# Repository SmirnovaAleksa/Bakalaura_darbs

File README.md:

# Bakalaura_darbs
Working with ESP32 and STM32 for plant monitoring system

Final board

3D view

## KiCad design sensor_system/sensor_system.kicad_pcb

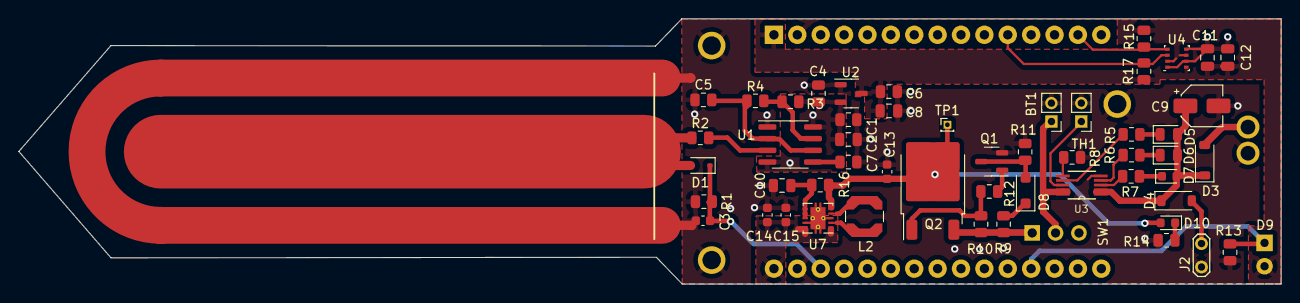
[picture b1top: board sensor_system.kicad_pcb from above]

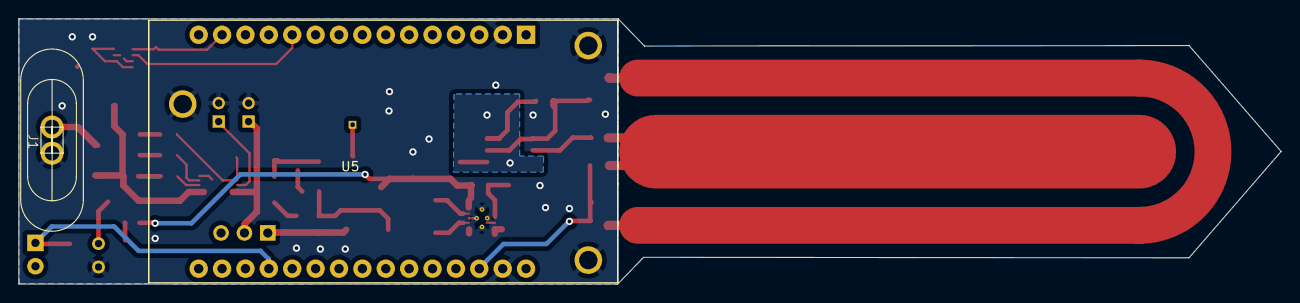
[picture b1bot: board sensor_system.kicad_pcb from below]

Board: 2 copper layers, 137.1 x 28.8 mm, 56 parts (2 on the bottom side), 35 nets.

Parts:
BT1: 3V7; PinHeader_1x02_P2.00mm_Vertical
C1, C6: 100n; R_0805_2012Metric
C2: 1.4u; C_0805_2012Metric
C3: 1uF; C_0603_1608Metric
C4: 100nF; R_0805_2012Metric
C5: 470pF; R_0805_2012Metric
C7: 10nF; R_0805_2012Metric
C8: 4.7u; C_0805_2012Metric
C9: 10u; CP_Elec_4x5.4
C10, C11, C12: 0u1; C_0805_2012Metric
C13, C14, C15: 10u; C_0603_1608Metric
D1: 1N4148WS; D_SOD-323
D3, D4: 1N5817; D_SOD-123
D5: PG Zaļa; LED_0805_2012Metric
D6: STAT2; LED_0805_2012Metric
D7: STAT1; LED_0603_1608Metric
D8: 3V; D_SOD-123F
D9: D_Photo; LED_D5.0mm
D10: ON/OFF; LED_0603_1608Metric
J1: Magnetic connector
J2: Solar_panels; TestPoint_2Pads_Pitch2.54mm_Drill0.8mm
L2: 2u2; L_Coilcraft_LPS4018
Q1: SBC817; SOT-23-3
Q2: MJD45H11; TO-252-2
R1: 1M; R_0805_2012Metric
R2, R13: 10k; R_0805_2012Metric
R3, R5: 330; R_0805_2012Metric
R4: 1.6k; R_0805_2012Metric
R6, R7, R14: 470; R_0805_2012Metric
R8: 1k; R_0805_2012Metric
R9: 120; R_0805_2012Metric
R10, R15, R17: 4k7; R_0805_2012Metric
R11: 180; R_0805_2012Metric
R12: 220; R_0805_2012Metric
R16: 100; R_0805_2012Metric
SW1: SW_DPDT_x2; PinHeader_1x03_P2.54mm_Horizontal
TH1: 10k; PinHeader_1x02_P2.00mm_Vertical
TP1: TestPoint; PinHeader_1x01_P1.00mm_Vertical
U1: TLC555xD; SOIC-8_3.9x4.9mm_P1.27mm
U2: XC6206PxxxMR; SOT-23-3
U3: MCP73833; SOP50P490X110-10N
U4: BME280; Bosch_LGA-8_2.5x2.5mm_P0.65mm_ClockwisePinNumbering
U5: ESP32-DEVKIT-V1; MODULE_ESP32_DEVKIT_V1
U7: TPS63002; Texas_DRC0010J_ThermalVias

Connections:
3V: C1.1, C2.1, C4.2, R3.1, U1.4 (R), U1.8 (VCC), U2.2 (VO)
3V3: C6.1, C8.1, C11.1, C12.1, D9.2 (A), R15.2, R17.2, U2.3 (VI), U4.2 (CSB), U4.6 (VDDIO), U4.8 (VDD), U5.1 (3V3)
/power_supply/5V: C14.1, C15.1, U5.30 (VIN), U7.1 (VOUT), U7.10 (FB)
Earth: BT1.2 (-), C1.2, C2.2, C3.1, C4.1, C5.1, C6.2, C7.2, C8.2, C9.2, C10.2, C11.2, C12.2, C13.2, C14.2, C15.2, J1.1, J2.1, Q1.2 (E), R1.1, R8.1, R11.2, R13.2, R14.1, TH1.2, U1.1 (GND), U2.1 (GND), U3.5 (VSS), U4.1 (GND), U4.5 (SDO), U4.7 (GND), U5.2 (GND), U5.29 (GND), U7.3 (PGND), U7.9 (GND), U7.11 (PGND)
unnamed: BT1.1 (+), SW1.2 (B), U3.9 (Vbat), U3.10 (Vbat)
unnamed: D1.2 (A), R2.1
unnamed: D3.2 (A), J1.2
unnamed: C9.1, D3.1 (K), D4.1 (K), D5.2 (A), D6.2 (A), D7.2 (A), U3.1 (VDD), U3.2 (VDD)
unnamed: D4.2 (A), J2.2
unnamed: D5.1 (K), R5.1
unnamed: D6.1 (K), R6.1
unnamed: D7.1 (K), R7.1
unnamed: D8.2 (A), Q1.3 (B), R11.1
unnamed: D8.1 (K), R9.2
unnamed: D9.1 (K), R13.1, U5.19 (D34)
unnamed: C13.1, D10.2 (A), Q2.2 (C), R16.1, TP1.1, U7.5 (VIN)
unnamed: D10.1 (K), R14.2
unnamed: Q1.1 (C), R12.2
unnamed: Q2.1 (B), R10.2, R12.1
unnamed: Q2.3 (E), R9.1, R10.1, SW1.1 (A)
unnamed: C7.1, U1.5 (CV)
unnamed: R3.2, R4.2, U1.7 (DIS)
unnamed: R2.2, U1.3 (Q)
unnamed: C5.2, R4.1, U1.2 (TR), U1.6 (THR)
unnamed: R5.2, U3.7 (PG)
unnamed: R8.2, U3.6 (PROG)
unnamed: R7.2, U3.3 (STAT1)
unnamed: R6.2, U3.4 (STAT2)
unnamed: TH1.1, U3.8 (THERM)
unnamed: C10.1, R16.2, U7.6 (EN), U7.7 (PS/SYNC), U7.8 (VINA)
unnamed: L2.1, U7.4 (L1)
unnamed: L2.2, U7.2 (L2)
SCL: R15.1, U4.4 (SCK), U5.14 (D22)
SDA: R17.1, U4.3 (SDI), U5.11 (D21)
Soil: C3.2, D1.1 (K), R1.2, U5.28 (D13)

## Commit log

2023-03-26 Elektriski principiālā shēma
2023-03-26 Ievads
2023-03-26 Linki
2023-03-26 Pievienoti footprint visām komponentēm
2023-03-26 Izveidots footprint magnetiskajam konetoram
2023-03-26 Iespiedplate v1
2023-03-29 Disaster in progress
2023-03-29 Board V1 with one mistake
2023-03-30 Borad v1
2023-04-03 BME280 schematic fix
2023-04-03 Board V2
2023-04-03 Add images
2023-04-03 Add links for bme280
2023-04-12 Board fix 2.0
2023-04-15 Final board
2023-04-15 Update board pictures
2023-04-15 Final board fix
2023-04-15 Add firebase links
2023-04-20 Add Elektriski principiālā shēmas apraksts
2023-04-20 Add Iespiedplate un BLE programmas kods
2023-04-21 Add ESP32 programmas apraksts
2023-04-21 Add code
2023-05-24 Update links
    update
2023-05-24 Testi
2023-05-24 Add graphs
2023-05-24 Update links
    AMS1117
2023-05-29 Update links
2023-06-05 Gala versija
2023-06-05 Delete
